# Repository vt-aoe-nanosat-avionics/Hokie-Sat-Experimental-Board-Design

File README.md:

## Hokie Sat Experimental Board Revision: 100 Pin Configuration

# Test

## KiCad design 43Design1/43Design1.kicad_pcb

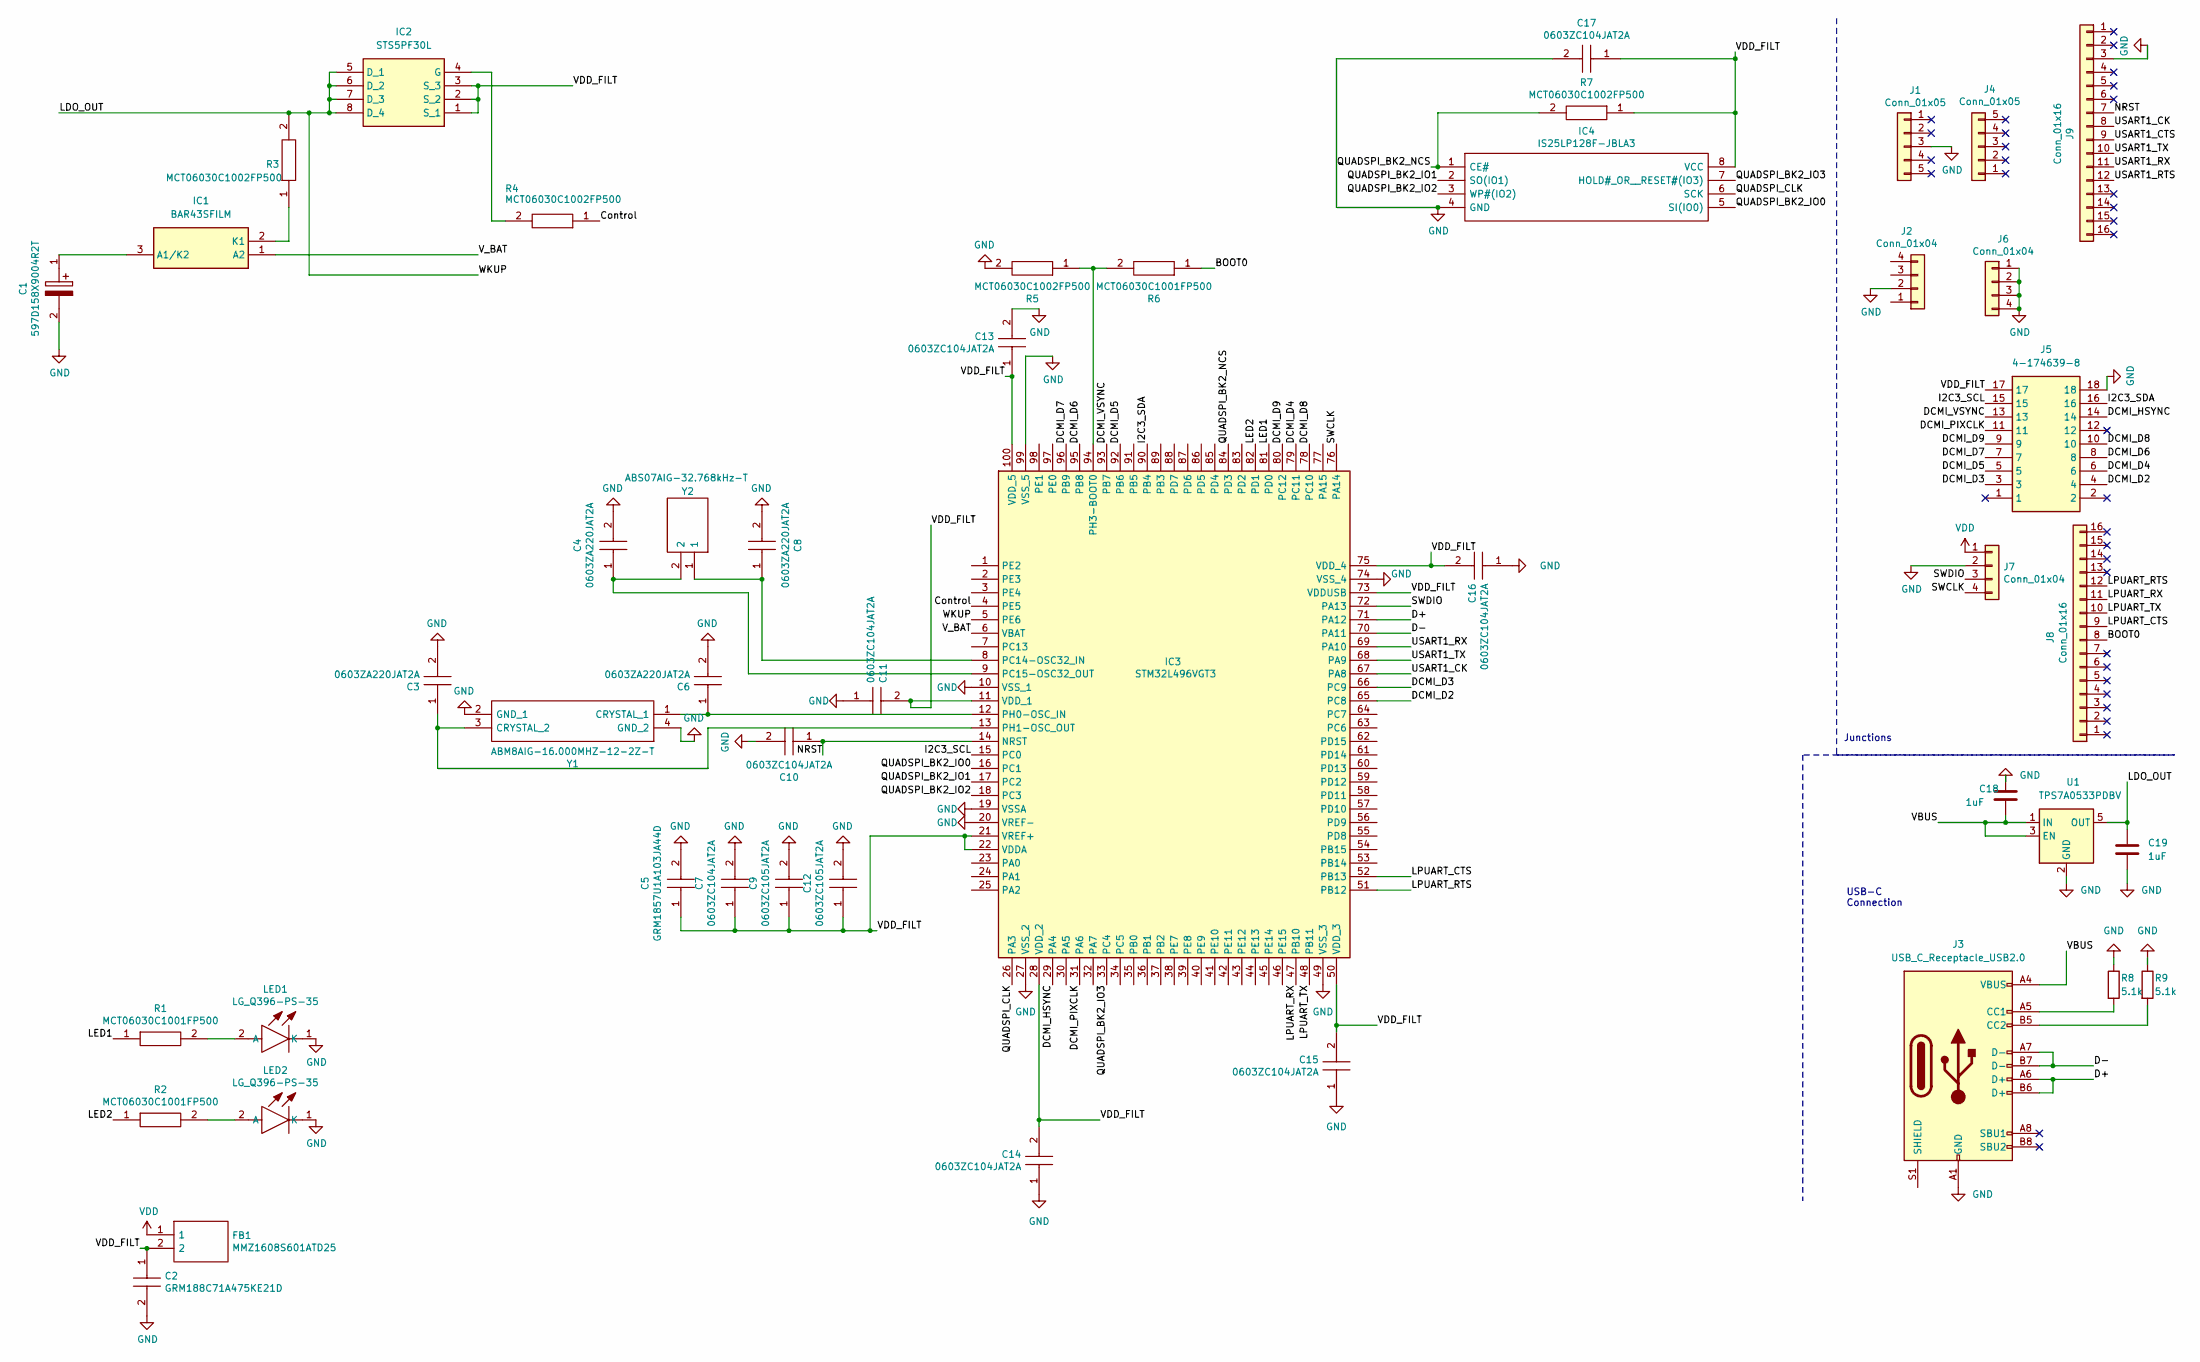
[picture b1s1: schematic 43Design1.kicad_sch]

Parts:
C1: 597D158X9004R2T; CAPPC5660X400N; Manufacturer_Part_Number 597D158X9004R2T; Mouser Part Number 71-597D158X9004R2T
C2: GRM188C71A475KE21D; CAPC1608X90N; Manufacturer_Part_Number GRM188C71A475KE21D; Mouser Part Number 81-GRM188C71A475KE2D
C3, C4, C6, C8: 0603ZA220JAT2A; CAPC1608X90N; Manufacturer_Part_Number 0603ZA220JAT2A; Mouser Part Number 581-0603ZA220JAT2A
C5: GRM1857U1A103JA44D; CAPC1608X50N; Manufacturer_Part_Number GRM1857U1A103JA44D; Mouser Part Number 81-GRM1857U1A103JA4D
C7, C10, C11, C13, C14, C15, C16, C17: 0603ZC104JAT2A; CAPC1608X90N; Manufacturer_Part_Number 0603ZC104JAT2A; Mouser Part Number 581-0603ZC104JAT2A
C9, C12: 0603ZC105JAT2A; CAPC1608X90N; Manufacturer_Part_Number 0603ZC105JAT2A; Mouser Part Number 581-0603ZC105JAT2A
C18, C19: 1uF; CAPC1608X90N
FB1: MMZ1608S601ATD25; BEADC1608X95N; Manufacturer_Part_Number MMZ1608S601ATD25; Mouser Part Number 810-MMZ1608S601ATD25
IC1: BAR43SFILM; SOTFL50P160X78-3N; Manufacturer_Part_Number BAR43SFILM; Mouser Part Number 511-BAR43SFILM
IC2: STS5PF30L; SOIC127P600X175-8N; Manufacturer_Part_Number STS5PF30L; Mouser Part Number 511-STS5PF30L
IC3: STM32L496VGT3; QFP50P1600X1600X160-100N; Manufacturer_Part_Number STM32L496VGT3; Mouser Part Number 511-STM32L496VGT3
IC4: IS25LP128F-JBLA3; SOIC127P790X216-8N; Manufacturer_Part_Number IS25LP128F-JBLA3; Mouser Part Number 870-IS25LP128F-JBLA3
J1, J4: Conn_01x05; PinSocket_1x5_TartanArtibeus
J2, J7: Conn_01x04; PinSocket_4x1_TartanArtibeus
J3: USB_C_Receptacle_USB2.0; USB_C_Receptacle_XKB_U262-16XN-4BVC11
J5: 4-174639-8; 41746398; Mouser Part Number 571-4-174639-8
J6: Conn_01x04; MountingHoles_TartanArtibeus
J8, J9: Conn_01x16; PinSocket_1x16_TartanArtibeus
LED1, LED2: LG_Q396-PS-35; LGQ396PS35; Manufacturer_Part_Number LG Q396-PS-35; Mouser Part Number 720-LGQ396A3964
R1, R2, R6: MCT06030C1001FP500; RESC1608X55N; Manufacturer_Part_Number MCT06030C1001FP500; Mouser Part Number 594-MCT06030C1001FP5
R3, R4, R5, R7: MCT06030C1002FP500; RESC1608X55N; Manufacturer_Part_Number MCT06030C1002FP500; Mouser Part Number 594-MCT06030C1002FP5
R8, R9: 5.1k; RESC1608X55N
U1: TPS7A0533PDBV; SOT-23-5
Y1: ABM8AIG-16.000MHZ-12-2Z-T; ABM8AIG25000MHZ122ZT3; Manufacturer_Part_Number ABM8AIG-16.000MHZ-12-2Z-T; Mouser Part Number 815-ABM8AIG16122ZT
Y2: ABS07AIG-32.768kHz-T; ABS07AIG32768kHz71T; Manufacturer_Part_Number ABS07AIG-32.768kHz-T; Mouser Part Number 815-S07AIG-32.768T

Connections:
/BOOT0: J8.8, R6.1
/Control: IC3.4 (PE5), R4.1
/D+: IC3.71 (PA12), J3.A6 (D+), J3.B6 (D+)
/D-: IC3.70 (PA11), J3.A7 (D-), J3.B7 (D-)
/DCMI_D2: IC3.65 (PC8), J5.4
/DCMI_D3: IC3.66 (PC9), J5.3
/DCMI_D4: IC3.79 (PC11), J5.6
/DCMI_D5: IC3.92 (PB6), J5.5
/DCMI_D6: IC3.95 (PB8), J5.8
/DCMI_D7: IC3.96 (PB9), J5.7
/DCMI_D8: IC3.78 (PC10), J5.10
/DCMI_D9: IC3.80 (PC12), J5.9
/DCMI_HSYNC: IC3.29 (PA4), J5.14
/DCMI_PIXCLK: IC3.31 (PA6), J5.11
/DCMI_VSYNC: IC3.93 (PB7), J5.13
/I2C3_SCL: IC3.15 (PC0), J5.15
/I2C3_SDA: IC3.90 (PB4), J5.16
/LDO_OUT: C19.1, IC2.5 (D_1), IC2.6 (D_2), IC2.7 (D_3), IC2.8 (D_4), IC3.5 (PE6), R3.2, U1.5 (OUT)
/LED1: IC3.81 (PD0), R1.1
/LED2: IC3.82 (PD1), R2.1
/LPUART_CTS: IC3.52 (PB13), J8.9
/LPUART_RTS: IC3.51 (PB12), J8.12
/LPUART_RX: IC3.47 (PB10), J8.11
/LPUART_TX: IC3.48 (PB11), J8.10
/NRST: C10.1, IC3.14 (NRST), J9.7
/QUADSPI_BK2_IO0: IC3.16 (PC1), IC4.5 (SI(IO0))
/QUADSPI_BK2_IO1: IC3.17 (PC2), IC4.2 (SO(IO1))
/QUADSPI_BK2_IO2: IC3.18 (PC3), IC4.3 (WP#(IO2))
/QUADSPI_BK2_IO3: IC3.33 (PC4), IC4.7 (HOLD#_OR__RESET#(IO3))
/QUADSPI_BK2_NCS: IC3.84 (PD3), IC4.1 (CE#), R7.2
/QUADSPI_CLK: IC3.26 (PA3), IC4.6 (SCK)
/SWCLK: IC3.76 (PA14), J7.4
/SWDIO: IC3.72 (PA13), J7.3
/USART1_CK: IC3.67 (PA8), J9.8
/USART1_CTS: J9.9
/USART1_RTS: J9.12
/USART1_RX: IC3.69 (PA10), J9.11
/USART1_TX: IC3.68 (PA9), J9.10
/VBUS: C18.2, J3.A4 (VBUS), J3.A9 (VBUS), J3.B4 (VBUS), J3.B9 (VBUS), U1.1 (IN), U1.3 (EN)
/VDD_FILT: C2.1, C5.1, C7.1, C9.1, C11.2, C12.1, C13.1, C14.2, C15.2, C16.2, C17.1, FB1.2, IC2.1 (S_1), IC2.2 (S_2), IC2.3 (S_3), IC3.11 (VDD_1), IC3.21 (VREF+), IC3.22 (VDDA), IC3.28 (VDD_2), IC3.50 (VDD_3), IC3.73 (VDDUSB), IC3.75 (VDD_4), IC3.100 (VDD_5), IC4.8 (VCC), J5.17, R7.1
/V_BAT: IC1.1 (A2), IC3.6 (VBAT)
GND: C1.2, C2.2, C3.2, C4.2, C5.2, C6.2, C7.2, C8.2, C9.2, C10.2, C11.1, C12.2, C13.2, C14.1, C15.1, C16.1, C17.2, C18.1, C19.2, IC3.10 (VSS_1), IC3.19 (VSSA), IC3.20 (VREF-), IC3.27 (VSS_2), IC3.49 (VSS_3), IC3.74 (VSS_4), IC3.99 (VSS_5), IC4.4 (GND), J1.3, J2.2, J3.A1 (GND), J3.A12 (GND), J3.B1 (GND), J3.B12 (GND), J5.18, J6.1, J6.2, J6.3, J6.4, J7.2, J9.3, LED1.1 (K), LED2.1 (K), R5.2, R8.1, R9.1, U1.2 (GND), Y1.2 (GND_1), Y1.4 (GND_2); also elsewhere on the board
unnamed 42: C1.1, IC1.3 (A1/K2); also elsewhere on the board
unnamed: IC1.2 (K1), R3.1
unnamed: IC2.4 (G), R4.2
unnamed 45: C8.1, IC3.8 (PC14-OSC32_IN), Y2.1; also elsewhere on the board
unnamed 46: C4.1, IC3.9 (PC15-OSC32_OUT), Y2.2; also elsewhere on the board
unnamed 47: C6.1, IC3.12 (PH0-OSC_IN), Y1.1 (CRYSTAL_1); also elsewhere on the board
unnamed 48: C3.1, IC3.13 (PH1-OSC_OUT), Y1.3 (CRYSTAL_2); also elsewhere on the board
unnamed: IC3.94 (PH3-BOOT0), R5.1, R6.2
unnamed: J3.A5 (CC1), R8.2
unnamed: J3.B5 (CC2), R9.2
unnamed: LED1.2 (A), R1.2
unnamed: LED2.2 (A), R2.2
VDD: FB1.1, J7.1

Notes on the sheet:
Junctions
USB-C Connection

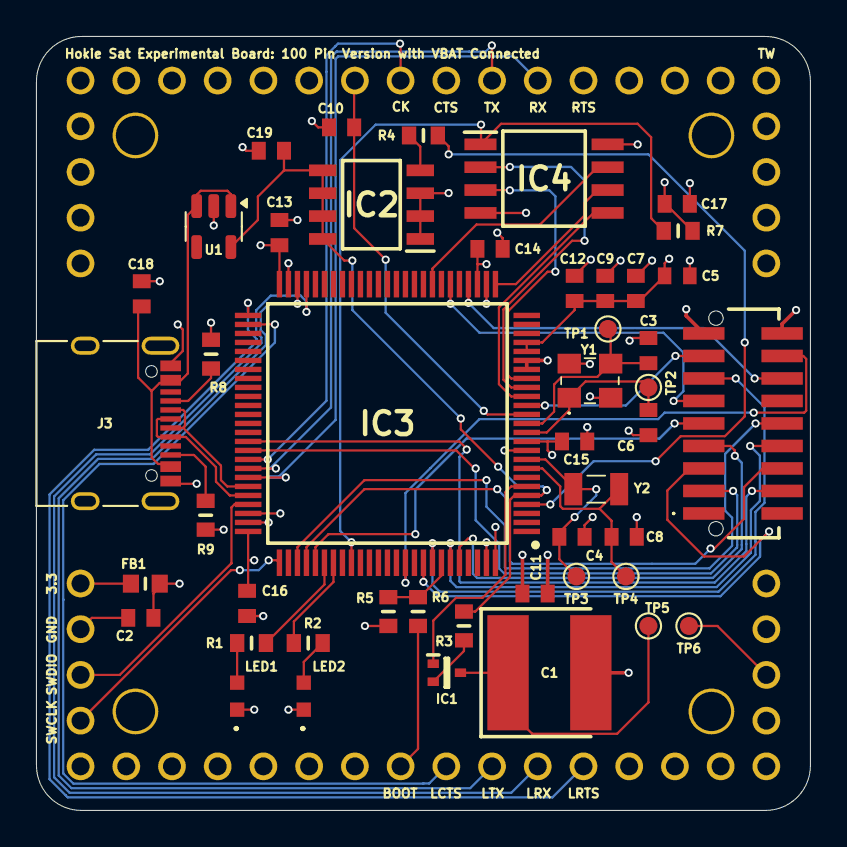
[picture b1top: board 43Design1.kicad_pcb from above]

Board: 4 copper layers, 43.0 x 43.0 mm, 53 parts (0 on the bottom side), 53 nets.

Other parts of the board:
TP1, TP2, TP3, TP4, TP5, TP6: TestPoint_Pad_D1.0mm

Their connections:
GND: TP6.1; also elsewhere on the board
unnamed 42: TP5.1; also elsewhere on the board
unnamed 45: TP4.1; also elsewhere on the board
unnamed 46: TP3.1; also elsewhere on the board
unnamed 47: TP2.1; also elsewhere on the board
unnamed 48: TP1.1; also elsewhere on the board

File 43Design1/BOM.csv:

"Reference","Value","Datasheet","Footprint","Qty","DNP"
"C1","597D158X9004R2T","http://www.vishay.com/doc?40047","ta-expt-v2-100:CAPPC5660X400N","1",""
"C2","GRM188C71A475KE21D","","ta-expt-v2-100:CAPC1608X90N","1",""
"C3,C4,C6,C8","0603ZA220JAT2A","https://componentsearchengine.com/Datasheets/1/06031A100FAT2A.pdf","ta-expt-v2-100:CAPC1608X90N","4",""
"C5","GRM1857U1A103JA44D","https://psearch.en.murata.com/capacitor/product/GRM1857U1A10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","ta-expt-v2-100:CAPC1608X50N","1",""
"C7,C10,C11,C13,C14,C15,C16,C17","0603ZC104JAT2A","https://componentsearchengine.com/Datasheets/1/06031A100FAT2A.pdf","ta-expt-v2-100:CAPC1608X90N","8",""
"C9,C12","0603ZC105JAT2A","https://componentsearchengine.com/Datasheets/1/06031A100FAT2A.pdf","ta-expt-v2-100:CAPC1608X90N","2",""
"C18,C19","1uF","~","ta-expt-v2-100:CAPC1608X90N","2",""
"FB1","MMZ1608S601ATD25","https://datasheet.datasheetarchive.com/originals/dk/DKDS-25/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","ta-expt-v2-100:BEADC1608X95N","1",""
"IC1","BAR43SFILM","https://www.mouser.com/ProductDetail/511-BAR43SFILM","ta-expt-v2-100:SOTFL50P160X78-3N","1",""
"IC2","SI4056ADY-T1-GE3","https://www.mouser.com/ProductDetail/78-SI4056ADY-T1-GE3","ta-expt-v2-100:SOIC127P600X175-8N","1",""
"IC3","STM32L496VGT3","https://www.mouser.com/ProductDetail/511-STM32L496VGT3","QFP50P1600X1600X160-100N","1",""
"IC4","IS25LP128F-JBLA3","http://www.issi.com/WW/pdf/25LP-WP128F.pdf","ta-expt-v2-100:SOIC127P790X216-8N","1",""
"J1,J4","Conn_01x05","~","ta-expt-v2-100:PinSocket_1x5_TartanArtibeus","2",""
"J2,J6,J7","Conn_01x04","~","-- mixed values --","3",""
"J3","USB_C_Receptacle_USB2.0","https://www.mouser.com/ProductDetail/Adafruit/4458?qs=xZ%2FP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","Connector_USB:USB_C_Receptacle_XKB_U262-16XN-4BVC11","1",""
"J5","4-174639-8","https://www.te.com/commerce/DocumentDelivery/DDEController?A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","ta-expt-v2-100:41746398","1",""
"J8,J9","Conn_01x16","~","ta-expt-v2-100:PinSocket_1x16_TartanArtibeus","2",""
"LED1,LED2","LG_Q396-PS-35","https://mouser.componentsearchengine.com/Datasheets/2/LG%20Q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","ta-expt-v2-100:LGQ396PS35","2",""
"R1,R2,R6","MCT06030C1001FP500","http://www.vishay.com/docs/28705/mcx0x0xpro.pdf","ta-expt-v2-100:RESC1608X55N","3",""
"R3,R4,R5,R7","MCT06030C1002FP500","http://www.vishay.com/docs/28705/mcx0x0xpro.pdf","ta-expt-v2-100:RESC1608X55N","4",""
"R8,R9","5.1k","MCT06030C5101FP500","ta-expt-v2-100:RESC1608X55N","2",""
"U1","TPS7A0533PDBV","https://www.ti.com/lit/ds/symlink/tps7a05.pdf","Package_TO_SOT_SMD:SOT-23-5","1",""
"Y1","ABM8AIG-16.000MHZ-12-2Z-T","https://abracon.com/AIGcrystals/ABM8AIG.pdf","ta-expt-v2-100:ABM8AIG25000MHZ122ZT3","1",""
"Y2","ABS07AIG-32.768kHz-T","https://abracon.com/AIGcrystals/ABS07AIG.pdf","ta-expt-v2-100:ABS07AIG32768kHz71T","1",""

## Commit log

2024-10-15 Updated workflow of new schematic
2024-10-15 Removed Double
2024-10-18 Updated Design and Added Gerber Files
2024-10-22 Adding addtional KiCad schematic into repository. Includes design 1 of 43 x 43 mm design, and will add alternative design by Wednesday
2024-10-22 Create README.md
    Added in a Readme
2024-10-22 Updating folder with everything that is needed, and also added in additional board with different design. Touched up some stuff too, but also need to add in datasheets and BOM
2024-10-22 Adding BOM
    BOM for Design 1 of 43 x 43 mm
2024-10-23 Updated 43 x 43 mm Design 2 with QUAD SPI BK 2 NCS. NEED TO BE CHANGED ON DESIGN 1 AS WELL. PCB NEEDS TO BE UPDATED ON BOTH OF THEM.
2024-10-23 Added new Gerbers and updated schematic accordingly with QUADSPI BK2 rewire. Also renamed everything with the design numbers.
2024-10-23 Removing a folder
2024-10-23 Updated ReamMe
2024-12-01 Added new updated PCB Design with LEDs. Also gave 3D models for some components.
